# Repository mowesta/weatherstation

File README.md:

# weatherstation
Source code and schematics for an Arduino-based weather station.

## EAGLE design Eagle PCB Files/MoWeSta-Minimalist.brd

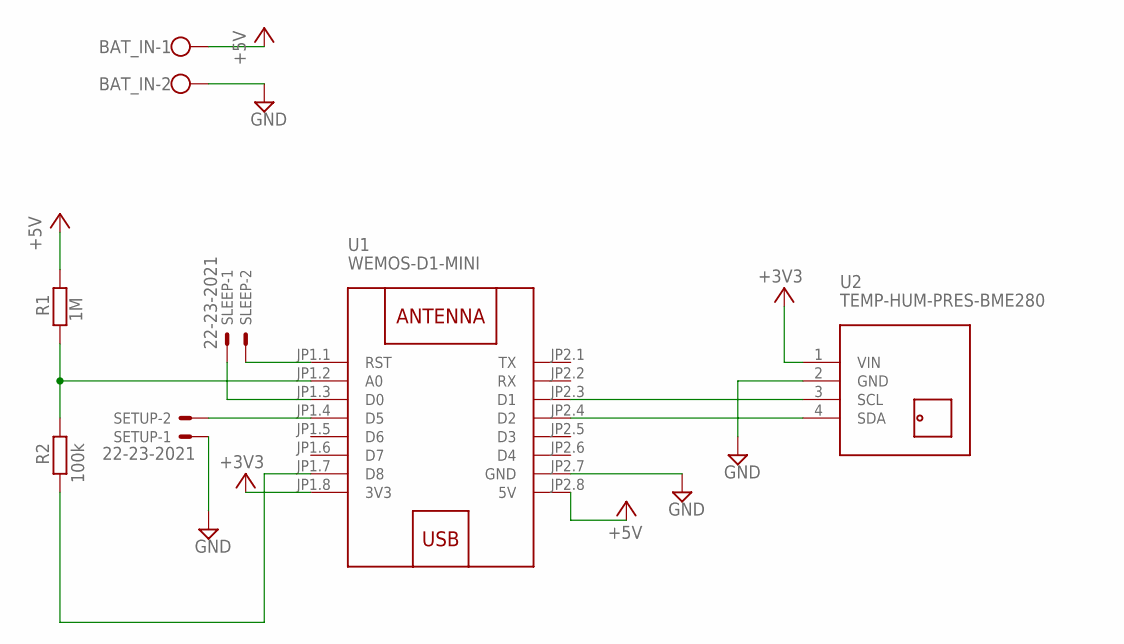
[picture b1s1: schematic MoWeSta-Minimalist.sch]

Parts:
BAT_IN: W237-102
R1: 1M; 0204/7
R2: 100k; 0204/7
SETUP: 22-23-2021
SLEEP: 22-23-2021
U1: WEMOS-D1-MINI
U2: TEMP-HUM-PRES-BME280

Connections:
+3V3: U1.JP1.8 (3V3), U2.1 (VIN)
+5V: BAT_IN.1, R1.2, U1.JP2.8 (5V)
GND: BAT_IN.2, SETUP.1, U1.JP2.7 (GND), U2.2 (GND)
unnamed: R1.1, R2.2, U1.JP1.2 (A0)
unnamed: SLEEP.2, U1.JP1.1 (RST)
unnamed: SLEEP.1, U1.JP1.3 (D0)
unnamed: SETUP.2, U1.JP1.4 (D5)
unnamed: U1.JP2.3 (D1), U2.3 (SCL)
unnamed: U1.JP2.4 (D2), U2.4 (SDA)
unnamed: R2.1, U1.JP1.7 (D8)

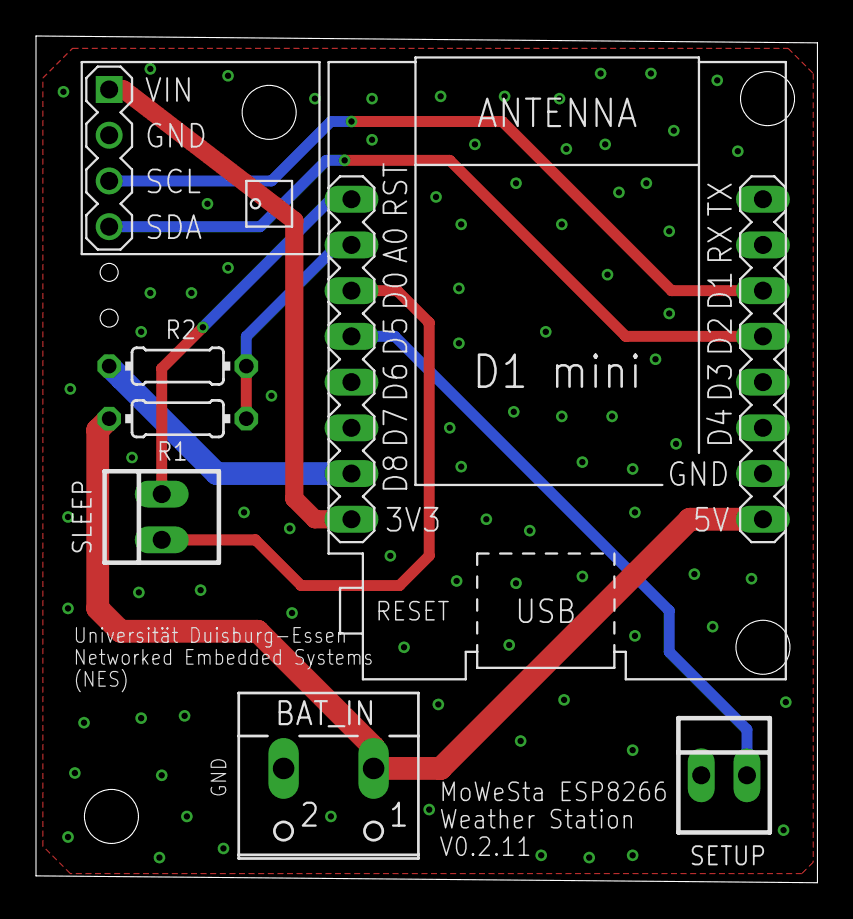
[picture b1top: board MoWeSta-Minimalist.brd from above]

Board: 2 copper layers, 43.4 x 47.0 mm, 7 parts (0 on the bottom side), 10 nets.

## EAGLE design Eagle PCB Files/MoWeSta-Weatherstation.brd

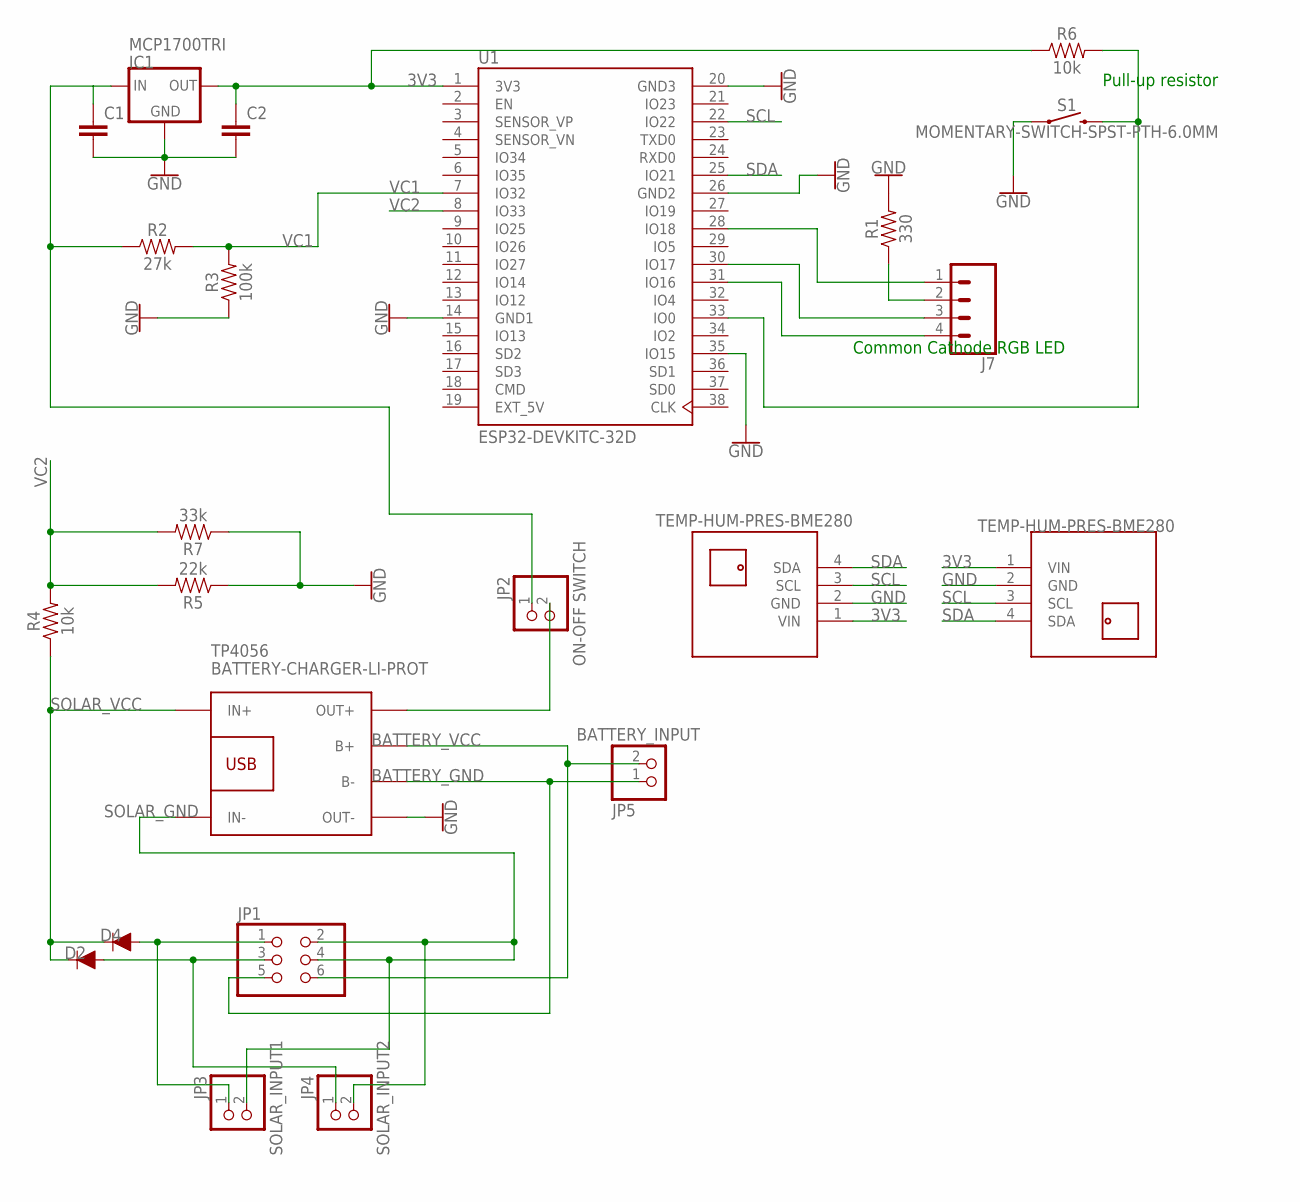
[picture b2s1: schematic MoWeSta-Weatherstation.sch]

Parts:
C1: 10nF; C050-025X075
C2: C-EU050-025X075; C050-025X075
D2, D4: 1A/50V/1.1V; DIODE-1N4001
IC1: MCP1700TRI; TO92-INLINE
J7: CONN_04; 1X04
JP1: PINHD-2X3/90; 2X03/90
JP2: ON-OFF SWITCH; 1X02
JP3: SOLAR_INPUT1; 1X02
JP4: SOLAR_INPUT2; 1X02
JP5: BATTERY_INPUT; 1X02
R1: 330; AXIAL-0.3
R2: 27k; AXIAL-0.3
R3: 100k; AXIAL-0.3
R4, R6: 10k; AXIAL-0.3
R5: 22k; AXIAL-0.3
R7: 33k; AXIAL-0.3
S1: MOMENTARY-SWITCH-SPST-PTH-6.0MM; TACTILE_SWITCH_PTH_6.0MM
TP4056: BATTERY-CHARGER-LI-PROT
U1: ESP32-DEVKITC-32D; MODULE_ESP32-DEVKITC-32D
U$3, U$4: TEMP-HUM-PRES-BME280

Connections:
3V3: C2.1, IC1.3 (OUT), R6.P$1 (1), U1.1 (3V3), U$3.1 (VIN), U$4.1 (VIN)
BATTERY_GND: JP1.5, JP5.1, TP4056.B-
BATTERY_VCC: JP1.6, JP5.2, TP4056.B+
EXT_5V: U1.19 (EXT_5V)
GND: C1.2, C2.2, IC1.1 (GND), R1.P$2 (2), R3.P$1 (1), R5.P$1 (1), R7.P$1 (1), S1.1, TP4056.OUT-, U1.14 (GND1), U1.20 (GND3), U1.26 (GND2), U1.35 (IO15), U$3.2 (GND), U$4.2 (GND)
unnamed: D2.A, JP1.3, JP4.1
unnamed: D4.A, JP1.1, JP3.1
unnamed: J7.2, R1.P$1 (1)
unnamed: C1.1, IC1.2 (IN), JP2.1, R2.P$1 (1)
unnamed: J7.1, U1.28 (IO18)
unnamed: JP2.2, TP4056.OUT+
unnamed: J7.4, U1.31 (IO16)
unnamed: R6.P$2 (2), S1.3 (2), U1.33 (IO0)
unnamed: J7.3, U1.30 (IO17)
SCL: U1.22 (IO22), U$3.3 (SCL), U$4.3 (SCL)
SDA: U1.25 (IO21), U$3.4 (SDA), U$4.4 (SDA)
SOLAR_GND: JP1.2, JP1.4, JP3.2, JP4.2, TP4056.IN-
SOLAR_VCC: D2.C, D4.C, R4.P$1 (1), TP4056.IN+
VC1: R2.P$2 (2), R3.P$2 (2), U1.7 (IO32)
VC2: R4.P$2 (2), R5.P$2 (2), R7.P$2 (2), U1.8 (IO33)

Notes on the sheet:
Pull-up resistor
Common Cathode RGB LED

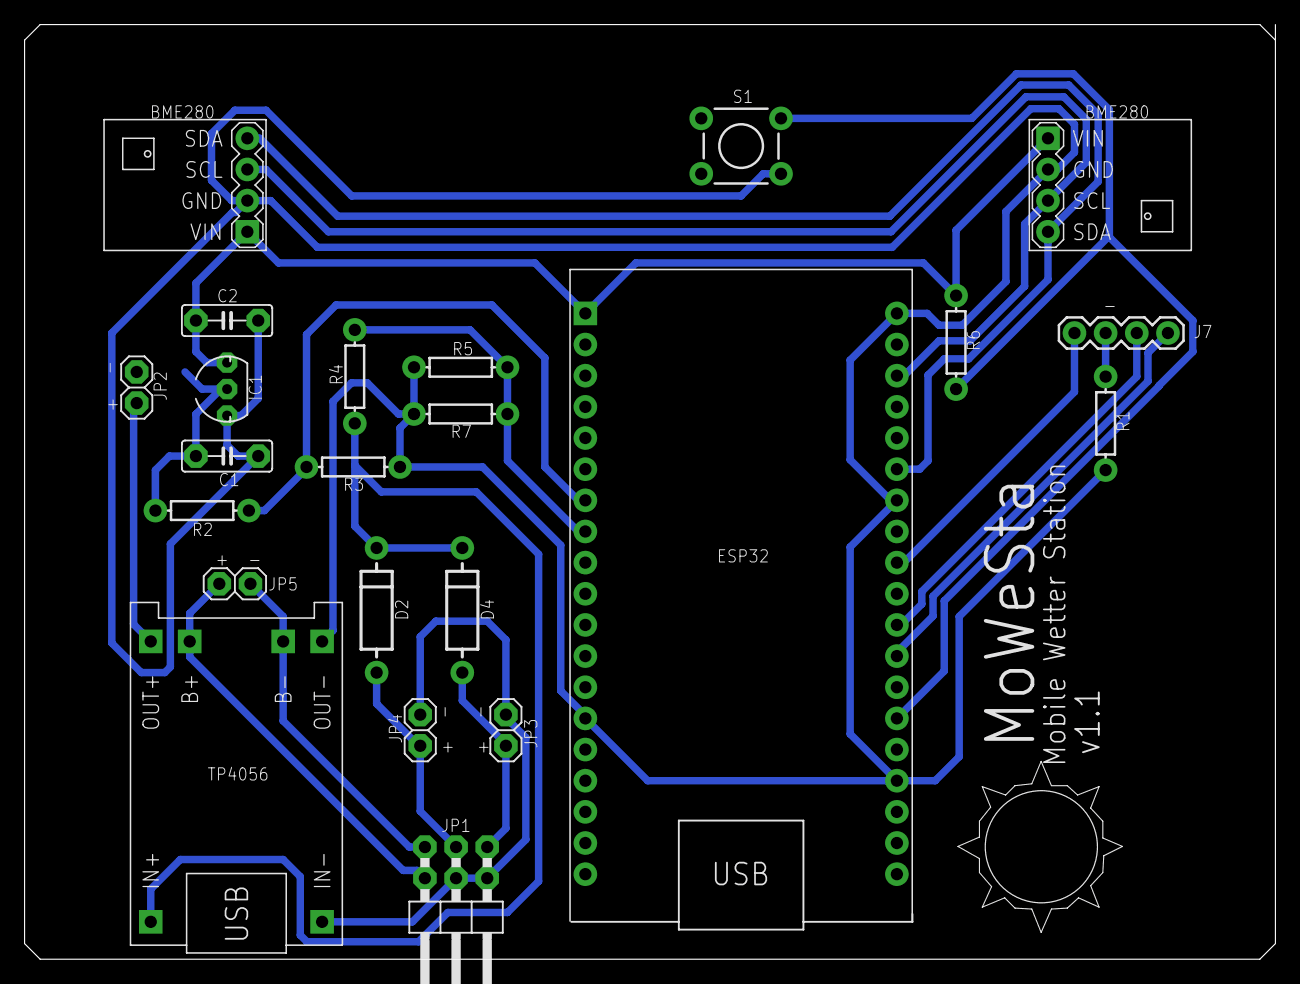
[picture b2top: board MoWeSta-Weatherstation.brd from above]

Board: 2 copper layers, 102.0 x 76.2 mm, 23 parts (0 on the bottom side), 19 nets.

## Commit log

2020-05-04 Solo Beginner Beispiel
2020-05-04 MoWeSta Wetterstation
2020-05-04 PCB Files
2020-05-04 3D-Print ready
2020-05-13 CAD-Files
2020-05-13 Panelhalter Fuß
2020-06-23 lib fix
2020-06-26 Fix sensor code, change protocol and fix synchronization.
    Multiply humidity value by 100 before sending it to the backend.
    Flatten json structure for receiving configuration information.
    Modify configuration protocol to avoid races in Android app.
2022-11-13 Added code and pcb for minimalistic station with ESP8266.

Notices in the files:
parts and their libraries:
diy-modules: Released under the Creative Commons Attribution 4.0 International License: http://creativecommons.org/licenses/by/4.0
SparkFun-Resistors: Licensing: Creative Commons ShareAlike 4.0 International - https://creativecommons.org/licenses/by-sa/4.0
